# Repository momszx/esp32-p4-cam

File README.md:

# ESP32-P4-CAM

A compact WiFi streaming camera built around the ESP32-P4. The camera streams live video over WiFi (RTSP, hardware H.264). The design uses a two-board stack, FRONT and MAIN, both 45 × 45 mm, with a 7 mm gap between them. Power comes from a single USB-C port that negotiates 9 V over USB Power Delivery.

This repository holds the hardware design (KiCad 10) and its documentation. There is no firmware in it yet.

| MAIN rev A, top (F) side | MAIN rev A, bottom (B) side |
|---|---|
|  |  |

## What it is

```
USB-C (PD 9 V, 5 V fallback) ─ TVS ─ eFuse ─ buck 3.3 V ─┬─ Waveshare ESP32-P4-Module (P4 + on-module ESP32-C6)
                                                          └─ CAM_3V3 load switch ─ OV5640 camera module

OV5640 ─ MIPI CSI-2 (2 lanes) ─ ESP32-P4 ISP ─ H.264 ─ RTSP ─ esp-hosted (SDIO) ─ ESP32-C6 WiFi ─ u.FL antenna
```

- **Compute:** a [Waveshare ESP32-P4-Module](https://www.waveshare.com/wiki/ESP32-P4-Module). The module carries an ESP32-P4 with 32 MB PSRAM in the package, 16 MB of flash, and an **ESP32-C6 on the module itself**, which provides WiFi to the P4 over SDIO through esp-hosted. The module is mounted on the bottom side of MAIN and soldered by hand.
- **Camera:** an OV5640 connected over MIPI CSI-2 (2 lanes), using a 15-pin, 1.0 mm FPC with the Raspberry Pi pinout. The camera module must have its own oscillator and LDOs.
- **Power:** USB-C PD sink, VBUS limited to 9 V.
  - A WCH CH224A negotiates 9 V. It is configured with a fixed resistor strap and its PG pin goes to a GPIO.
  - A TI TPS259470 eFuse provides OVLO, UVLO, current limit, reverse blocking and auto-retry.
  - A TI TPS62933F forced-PWM buck produces the 3.3 V rail.
  - USB-C is the only power input.
- **Programming:** the first flash goes over USB-C to the P4's built-in USB-Serial-JTAG (GPIO 24/25, Full Speed only). After that, both the P4 and the C6 are updated over the air (OTA).
- **Stack:**
  - **FRONT** board: lens cut-out, IR LEDs and driver, PDM microphone.
  - **MAIN** board: everything else.
  - The two boards are joined by 4 M2 standoffs plus a 2 × 10, 1.27 mm board-to-board header (J5). The camera FFC plugs into J2 on MAIN.

Rev A is a **proof-of-concept prototype**. Its job is to prove the core path: USB-C PD → eFuse → buck → P4 → OV5640 → H.264 → RTSP over the C6. The target is 1080p30, running 24 hours without a reset. Blocks outside that path are either routed footprints that are not fitted (DNP: microSD, the IR branch) or not on the rev A board at all (rev B: the reset supervisor and the ICR; the CC-ADC tap and the Rd fallback stay in the schematic only).

## Current status (2026-10-13)

| Item | State |
|---|---|
| **MAIN rev A layout** | **Complete and reviewed.** 4 layers, JLC04101H-3313A, 45 × 45 mm. |
| Checks (`kicad-cli`, no zone refill) | **DRC 0 errors**, **0 unconnected**, **ERC 0**, **schematic ↔ board parity 0**. There are also 39 `track_width` warnings from a custom power-net rule (two of them are deliberate 0.3 mm pad-entry necks at U7); they were reviewed and accepted. |
| Ordering | **Conditional GO.** You can order once the owner checks in [`kicad/MAIN/fab/ORDERING.md`](kicad/MAIN/fab/ORDERING.md) are done: the JLC form settings, rotations in the placement preview, the USB-C shell legs, stock reservations and accepting the U5 second source (its pinout is already checked). |
| Open owner decisions | **Q6:** which side of J2 has the contacts, plus the FFC type. **Q17:** the mated height of J5. Neither one blocks PCB fabrication. The remaining BOM confirmations are listed in [`BOM_NOTES.md`](kicad/MAIN/fab/BOM_NOTES.md) §10. |
| **FRONT board** | **Not started.** Waiting on gate **G6**, which needs a stable image from MAIN bring-up (G5b) and the camera's STEP model. |
| Firmware | Not started in this repo. Rev A firmware constraints are listed in `ORDERING.md` ("Firmware rules for rev A"). |

> Since round 10 (2026-10-13) the board has **no unconnected items**. The DNP IR eFuse branch (U7, R73) is fully routed, so it can be fitted on a rev A board later without bodge wires. The CC option parts (the R4/R5 Rd fallback and the CC-ADC taps R35/R36, C29/C30, D21/D22) are in the schematic only; they are not on the rev A board.

## Key specs

| Parameter | Value |
|---|---|
| Function | WiFi live-view camera: RTSP stream, hardware H.264. Rev A target is 1080p30 (the real figure gets fixed at G0). |
| Host module | Waveshare ESP32-P4-Module: ESP32-P4NRW32 + 16 MB flash + on-module ESP32-C6H8 (SDIO). 25 × 25 × 3.3 mm, 88 castellated pads at a 1.0 mm pitch |
| Wireless | ESP32-C6 through esp-hosted. Antenna on the J4 u.FL (Hirose U.FL-R-SMT-1); the module's own IPEX connector is an alternative (antenna decision Q25 still open). |
| Camera | OV5640, MIPI CSI-2 with 2 lanes, through J2 (TE 1-84953-5, 15-pin, 1.0 mm FPC, Raspberry Pi pinout). Supplied from a switched CAM_3V3 rail (TPS22917). |
| Power input | USB-C 16-pin (HRO TYPE-C-31-M-12), USB PD sink at **9 V** via the WCH CH224A. Falls back to 5 V on a non-PD or PC port (reduced "LOW" mode). |
| Input protection | SMAJ10A TVS, plus a TI TPS259470ARPWR eFuse: UVLO 4.40 / 4.00 V, OVLO 10.87 / 9.88 V, ILIM 2.03 A, reverse blocking, auto-retry |
| 3.3 V rail | TI TPS62933F synchronous buck (FCCM): 3.33 V, 3 A, 1.2 MHz, 2.2 µH |
| Power budget (estimate, not yet measured) | About 2.2 W typical and 4.4 W peak with IR off; about 5.6 W peak at night with IR on (the IR is on FRONT). |
| MAIN PCB | 45 × 45 mm. 4 layers on **JLC04101H-3313A**, finished thickness 0.97 mm (order as 1.0 mm). ENIG finish, impedance control, components on both sides. |
| Impedance (L1 / L4, referenced to GND) | RF 50 Ω: 0.302 mm · CSI 100 Ω diff: 0.204 / 0.203 mm · USB 90 Ω diff: 0.262 / 0.203 mm |
| Layer usage | L1 signals + parts · L2 solid GND · L3 power islands + GND fill · L4 module + signals |
| Stack | FRONT + MAIN, **7 mm gap**. 4 × M2 standoffs on a 33.5 mm grid; the grid centre is (22.5; 25.0), 2.5 mm below the board centre. J5 is a 2 × 10, 1.27 mm board-to-board connector. |
| Assembly | 72 placements (47 top / 25 bottom), 40 BOM lines, all with LCSC numbers. The P4 module (U1) is soldered by hand after SMT. |
| User I/O | BOOT, RESET and USER buttons, a status LED, and 12 bottom-side test pads. The C6 UART/boot pad row (J7) is DNP. |

## Repository layout

```
.
├── README.md
├── docs/                      English documentation (primary from 2026-10-12 on)
│   ├── README.md              documentation index and conventions
│   ├── 00-requirements.md … 09-pcb-layers.md, 90-review-log.md
│   ├── img/                   board renders and routing snapshots
│   └── hu/                    Hungarian originals, frozen 2026-10-12 (no longer maintained)
├── kicad/
│   ├── MAIN/                  KiCad 10 project of the MAIN board, rev A
│   │   ├── ESP32-P4-CAM-MAIN.kicad_pro / .kicad_sch / .kicad_pcb / .kicad_dru
│   │   ├── 01_tap.kicad_sch        power: USB-C, CH224A, eFuse, buck, USB ESD
│   │   ├── 02_p4_modul.kicad_sch   ESP32-P4 module, RF/u.FL, straps, status LED, NTC
│   │   ├── 03_kamera.kicad_sch     camera FPC J2, CAM_3V3 load switch
│   │   ├── 04_prog_tp.kicad_sch    buttons, C6/UART0 pad row J7, test points
│   │   ├── 05_b2b_front.kicad_sch  J5 board-to-board header to FRONT, IR branch (DNP)
│   │   ├── 06_sd.kicad_sch         microSD (DNP)
│   │   ├── scripts/           layout automation (placement, routing, merge): see scripts/README.md
│   │   └── fab/               JLC fabrication + assembly package (Gerber, BOM, CPL, ORDERING.md); hu/ = frozen Hungarian originals
│   ├── lib/                   project library ESP32-P4-CAM: custom symbols + footprints
│   └── archive/               abandoned 2-layer 60 × 50 mm MAIN attempt (2026-10-09, not fully routed)
└── ref/                       third-party datasheets + Waveshare land pattern (local only, git-ignored)
```

`ref/` is excluded from the repository for copyright reasons. Download the files from the links in [Third-party references](#third-party-references).

## Documentation

The English documents are the primary source; [`docs/README.md`](docs/README.md) is the index, with the conventions and markers used throughout. The Hungarian originals in [`docs/hu/`](docs/hu/) (and [`kicad/MAIN/fab/hu/`](kicad/MAIN/fab/hu/)) were frozen on 2026-10-12 and are no longer maintained. **Where documents disagree, `05-architecture.md` wins.**

| Doc | Content |
|---|---|
| [00-requirements](docs/00-requirements.md) | Goal, mandatory requirements (K1–K8), extra features, document map |
| [01-esp32-p4](docs/01-esp32-p4.md) | ESP32-P4 research: variants, power, boot, camera interfaces |
| [02-esp32-c6-and-programming](docs/02-esp32-c6-and-programming.md) | C6 options, esp-hosted P4 ↔ C6 link, programming both chips, power |
| [03-camera-ov5640](docs/03-camera-ov5640.md) | OV5640 interface, FPC connector, camera power rails |
| [04-peripherals](docs/04-peripherals.md) | microSD, microphone, IR, buttons/LED, USB-C power |
| [**05-architecture**](docs/05-architecture.md) | **Authoritative.** Rev A plan (§0: fit/DNP, gates, procurement), primary-source facts, PCB stack and the frozen mechanical interface (§3.1a), stackup (§3.2), power tree and budget (§4), GPIO map, connectors, bring-up sequence (§15) |
| [06-floorplan](docs/06-floorplan.md) | Area and height budget (7 mm gap), floorplan, as-built placement |
| [07-bom-plan](docs/07-bom-plan.md) | BOM with MPN/LCSC numbers, value calculations, USB-C pin map |
| [08-diagrams](docs/08-diagrams.md) | Block and connection diagrams (Mermaid) derived from 05 |
| [09-pcb-layers](docs/09-pcb-layers.md) | As-built MAIN rev A layer plots (L1–L4, mask/silkscreen, 3D views), stackup and copper statistics |
| [90-review-log](docs/90-review-log.md) | Full history of the design and review rounds, with corrections |

## Opening and checking the design

You need **KiCad 10.0** or newer. The files use the KiCad 10 format (board version `20260206`) and do not open in KiCad 9.

1. Open `kicad/MAIN/ESP32-P4-CAM-MAIN.kicad_pro`.
   - The project library is resolved as `${KIPRJMOD}/../lib`, so keep the `kicad/` folder structure as it is.
2. Run the checks from the command line. On macOS, `kicad-cli` is at `/Applications/KiCad/KiCad.app/Contents/MacOS/kicad-cli`; on Linux and Windows it is on `PATH`.

   ```sh
   cd kicad/MAIN
   kicad-cli pcb drc --schematic-parity --severity-all --format json -o drc.json ESP32-P4-CAM-MAIN.kicad_pcb
   kicad-cli sch erc --severity-all --format json -o erc.json ESP32-P4-CAM-MAIN.kicad_sch
   ```

   Expected results:
   - DRC: **0 errors**, 39 `track_width` warnings, **0 unconnected**, **0 parity issues**.
   - ERC: **0**.
   - Write the reports somewhere outside the repo, or delete them afterwards.

3. **Refill and save zones only inside `kicad/MAIN`.**
   - The command is `kicad-cli pcb drc --refill-zones --save-board …`.
   - The `.kicad_pro` and `.kicad_dru` files must sit next to the board when you do this. If you refill outside the project folder, the project rules are lost, including the 1 mm edge clearance for power zones, and the fills come out wrong.

> [!WARNING]
> **The KiCad GUI can overwrite `.kicad_pro` with stale settings when it closes.**
>
> This has happened twice. Closing the GUI wrote back an old in-memory copy of the project, which reverted the 4-layer rules to 2-layer values. DRC then reported hundreds of errors.
>
> After every GUI session, run `git diff kicad/MAIN/ESP32-P4-CAM-MAIN.kicad_pro` and check the design rules:
> - min track 0.09 mm, min drill 0.2 mm, min via 0.45 mm, clearance 0.15 mm
> - netclasses: Default 0.15, PWR 0.4, PWR_LIGHT 0.3, RF_50 0.302, CSI_DIFF 0.204/0.203, USB 0.262/0.203
> - the `netclass_patterns`
>
> If they reverted, restore the file from git or re-run `kicad/MAIN/scripts/project_rules.py` (see the [scripts README](kicad/MAIN/scripts/README.md); it has hardcoded paths). Then re-run DRC. If scripts are modifying the board, do not keep it open in the GUI.

## Fabrication and ordering (quick start)

Everything you need is in [`kicad/MAIN/fab/`](kicad/MAIN/fab/). Start with **[`ORDERING.md`](kicad/MAIN/fab/ORDERING.md)**; the part-selection rationale is in [`BOM_NOTES.md`](kicad/MAIN/fab/BOM_NOTES.md).

1. Re-run the pre-order gate from `ORDERING.md` on the board you are about to order:
   - refill and save inside the project folder;
   - DRC without refill gives 0 errors, 0 unconnected, parity 0;
   - ERC gives 0.
   - If the board has changed, regenerate the package (`kicad-cli pcb export gerbers --check-zones …` and `pcb export drill --excellon-separate-th …`, then BOM/CPL).
2. Upload `gerber_jlc.zip`, `BOM_jlc.csv` and `CPL_jlc.csv` (72 rows) to JLCPCB.
3. Set the PCB form:
   - 4 layers, 45 × 45 mm, 1.0 mm thick;
   - **stackup JLC04101H-3313A**, **impedance control on**, **ENIG**;
   - tented vias;
   - frame rails on the top and bottom edges only, with **no tab on the right edge**.
4. Check rotation and pin 1 in the JLC placement preview, and decide how the USB-C shell legs get soldered.
5. Reserve the low-stock parts before you order.
6. The P4 module is **not** in the BOM. Solder it by hand, then do the pre-power ohmmeter checks from `ORDERING.md`.

## Design-review history

- **Round 7 (2026-10-10):** a 15-agent PCB review (7 domain experts, a sceptical re-measurer for each domain, and a gap-finder who wrote the summary) gave **NO-GO**. Findings included the buck hot loop, the RF reference plane, GND stitching, the BOM gate and the ESP_EN pull-up.
- **Round 8 (2026-10-10/11):** **two parallel fix passes**. Each agent worked on its own fenced board region and the changes were merged by UUID (`kicad/MAIN/scripts/pcbmerge.py`, `regioncheck.py`). An independent checker re-measured every fix.
- **Round 9 (2026-10-11):** a 16-agent final review gave **conditional GO**. No design changes were needed. The only critical item was stale zone fills, a process issue, fixed by refilling and saving inside the project folder.
- **Round 10 (2026-10-13):** an external reviewer flagged the 12 unconnected items on DNP parts that rounds 8/9 had accepted. The IR eFuse branch (U7/R73) was routed so it can be fitted later. A routing attempt for the CC option group failed the independent check, so those 8 parts stay in the schematic only and are no longer on the board. Result: **0 unconnected**, BOM and CPL unchanged.

Details are in [`docs/90-review-log.md`](docs/90-review-log.md).

## Gates (rev A)

Full definitions and exit criteria are in [`05-architecture.md` §0.2](docs/05-architecture.md).

| Gate | Content | Status |
|---|---|---|
| G0 | Dev-kit stream test: OV5640 → ISP → H.264 → RTSP over the C6, a 24-hour soak, and current measurements. Freeze the SDK and component versions. | open |
| G1 | CH224A breakout bench test: 9 V PDO, strap, PG polarity, DP/DM left unconnected | open |
| G2 | Module schematic, footprint and antenna decision | partial: footprint built from the Waveshare land pattern and verified; module schematic questions and antenna choice still open |
| G3 | Freeze the camera module: lens, STEP model, FFC lengths, final J2 contact side (Q6) and CSI pin order (Q24) | open |
| G4 | BOM sheet complete (MPN / LCSC for every fitted part) | **closed for rev A** (2026-10-11) |
| G5 | MAIN schematic → layout → DRC → order | layout done, **conditional GO**; next is the order (see ORDERING.md) |
| G5b | Bring-up: MAIN on its own, camera on a 50–100 mm FFC, CSI soak test with error counters | pending |
| G6 | FRONT board: IR, microphone (ICR in rev B) | not started; begins after G5b |

## Third-party references

The datasheets are **not** redistributed in this repository. Get them from the vendors:

- **TI TPS25947 / TPS259470 eFuse** (the TPS259470ARPWR is a TPS25947xx variant). Datasheet SLVSFC9: <https://www.ti.com/lit/ds/symlink/tps25947.pdf>. Product page: <https://www.ti.com/product/TPS25947>
- **TI TPS62933 / TPS62933F buck.** Datasheet SLUSEA4: <https://www.ti.com/lit/ds/symlink/tps62933.pdf>. Product page: <https://www.ti.com/product/TPS62933>
- **WCH CH224 (CH224A / CH224Q) USB PD sink.** Product page: <https://www.wch-ic.com/products/CH224.html> (Chinese site: <https://www.wch.cn/products/CH224.html>). The design used the Chinese datasheet "CH224 手册1", v2.1.
- **Waveshare ESP32-P4-Module.** Wiki with pinout, schematic and the PCB land-pattern ZIP: <https://www.waveshare.com/wiki/ESP32-P4-Module>
- **Espressif ESP32-P4:**
  - product page: <https://www.espressif.com/en/products/socs/esp32-p4>
  - datasheet: <https://www.espressif.com/sites/default/files/documentation/esp32-p4_datasheet_en.pdf>
  - technical reference manual: <https://www.espressif.com/sites/default/files/documentation/esp32-p4_technical_reference_manual_en.pdf>
  - ESP-IDF programming guide: <https://docs.espressif.com/projects/esp-idf/en/latest/esp32p4/>
- **Related software:**
  - esp-hosted-mcu: <https://github.com/espressif/esp-hosted-mcu>
  - esp-video-components (esp_cam_sensor): <https://github.com/espressif/esp-video-components>
- **Stackup and impedance:** JLCPCB impedance calculator: <https://jlcpcb.com/pcb-impedance-calculator>

## License

Private project — all rights reserved (no license granted yet).

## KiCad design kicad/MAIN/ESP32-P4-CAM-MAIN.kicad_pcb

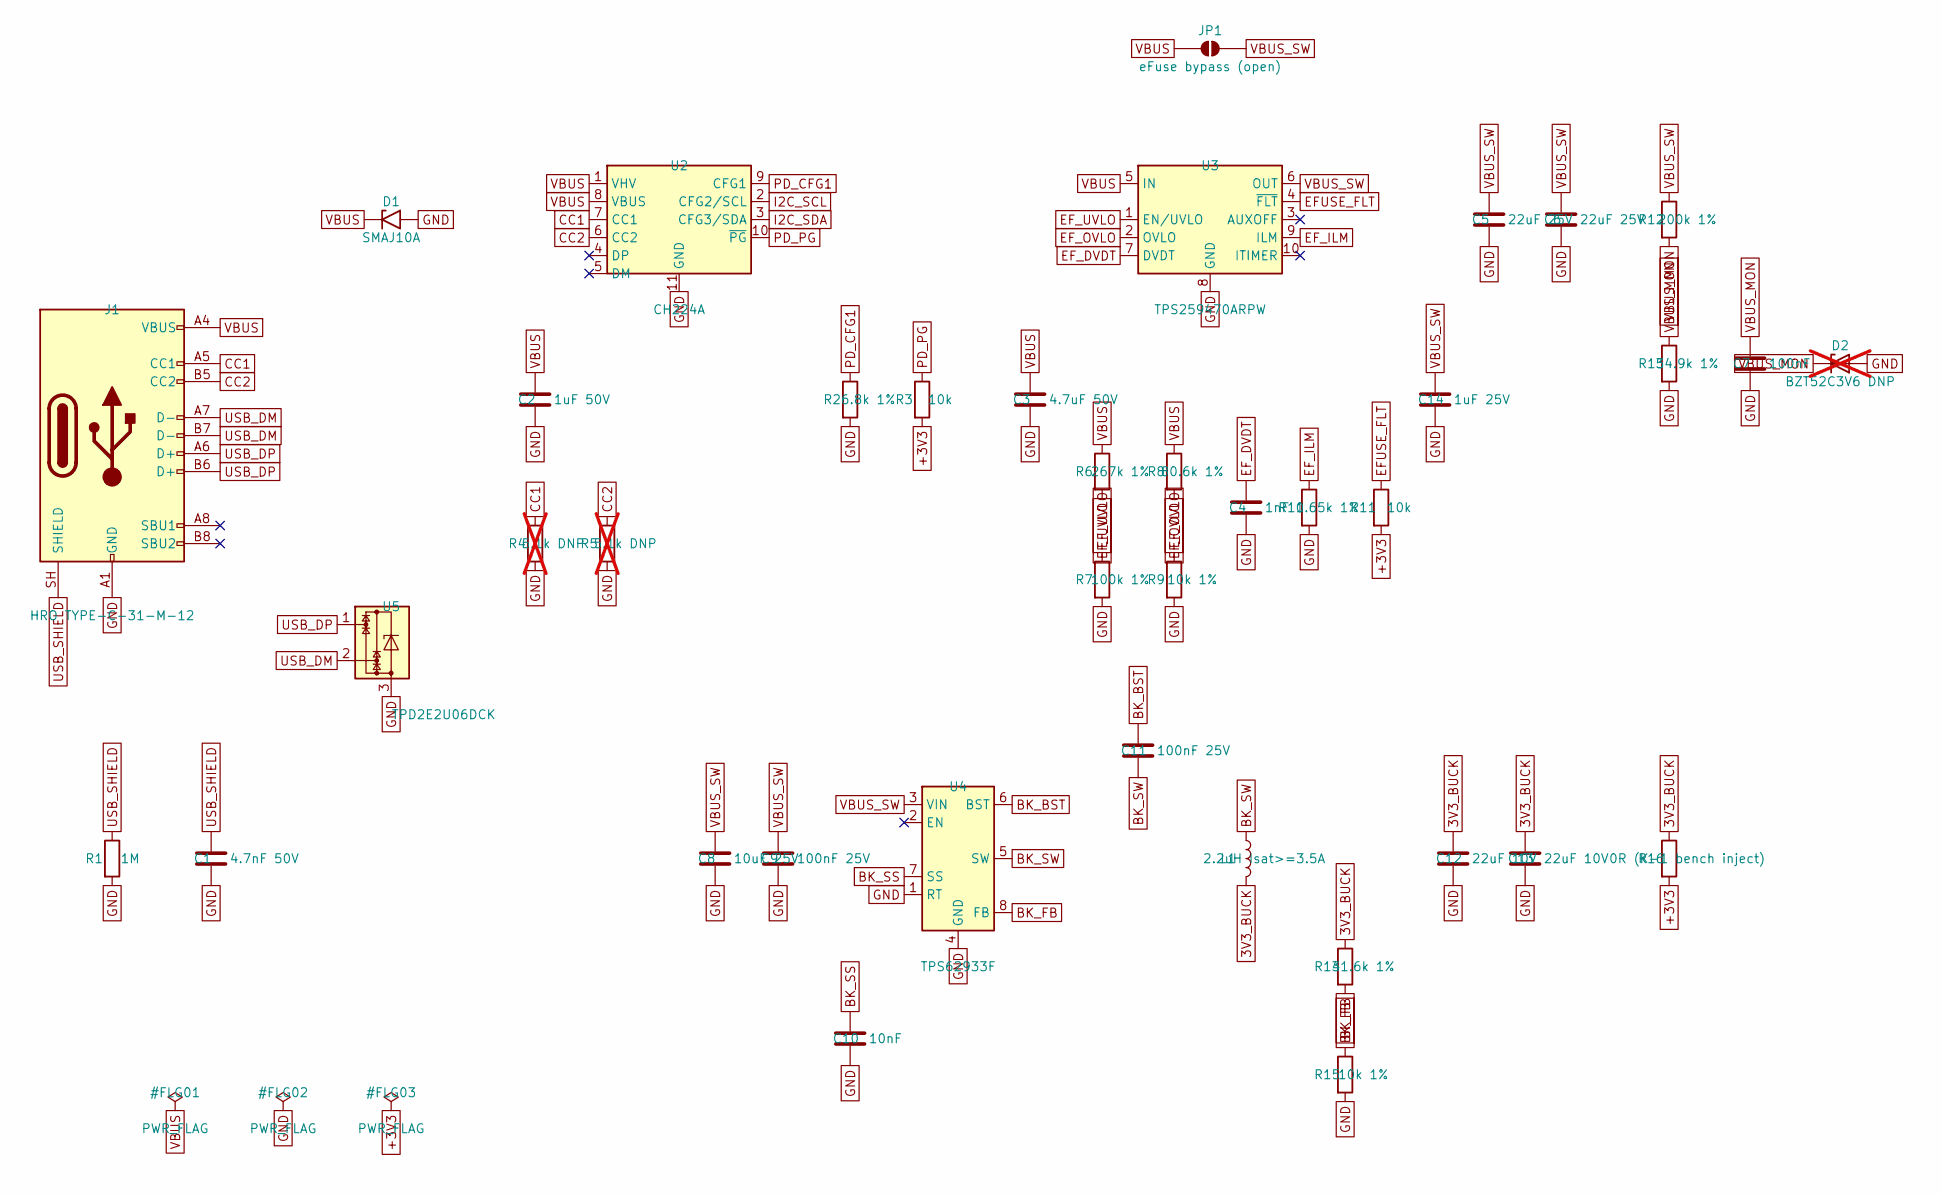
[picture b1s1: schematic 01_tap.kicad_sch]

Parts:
C1: 4.7nF 50V; C_0603_1608Metric; MPN CC0603KRX7RABB472; LCSC C596328
C2: 1uF 50V; C_0603_1608Metric; MPN CL10A105KB8NNNC; LCSC C15849
C3: 4.7uF 50V; C_0805_2012Metric; MPN CL21A475KBQNNNE; LCSC C98192
C4: 1nF; C_0603_1608Metric; MPN CL10B102KB8NNNC; LCSC C1588
C5, C6: 22uF 25V; C_1210_3225Metric; MPN CL32A226KAJNNNE; LCSC C52306
C7: 100nF; C_0603_1608Metric; MPN CC0603KRX7R9BB104; LCSC C14663
C8: 10uF 25V; C_0805_2012Metric; MPN CL21A106KAYNNNE; LCSC C15850
C9, C11: 100nF 25V; C_0603_1608Metric; MPN CC0603KRX7R9BB104; LCSC C14663
C10: 10nF; C_0603_1608Metric; MPN 0603B103K500NT; LCSC C57112
C12, C13: 22uF 10V; C_0805_2012Metric; MPN CL21A226MAQNNNE; LCSC C45783
C14: 1uF 25V; C_0603_1608Metric; MPN CL10B105KA8NNNC; LCSC C29936
D1: SMAJ10A; D_SMA; MPN SMAJ10A-13-F; LCSC C134939
D2: BZT52C3V6 DNP; D_SOD-123; not fitted
J1: HRO TYPE-C-31-M-12; USB_C_Receptacle_HRO_TYPE-C-31-M-12; MPN TYPE-C-31-M-12; LCSC C165948
JP1: eFuse bypass (open); SolderJumper-2_P1.3mm_Open_RoundedPad1.0x1.5mm
L1: 2.2uH Isat>=3.5A; L_Taiyo-Yuden_NR-50xx; MPN NRS5024T2R2NMGJ; LCSC C222926
R1: 1M; R_0603_1608Metric; MPN 0603WAF1004T5E; LCSC C22935
R2: 6.8k 1%; R_0603_1608Metric; MPN 0603WAF6801T5E; LCSC C23212
R3, R11: 10k; R_0603_1608Metric; MPN 0603WAF1002T5E; LCSC C25804
R4, R5: 5.1k DNP; R_0603_1608Metric; not fitted
R6: 267k 1%; R_0603_1608Metric; MPN 0603WAF2673T5E; LCSC C22963
R7: 100k 1%; R_0603_1608Metric; MPN 0603WAF1003T5E; LCSC C25803
R8: 80.6k 1%; R_0603_1608Metric; MPN 0603WAF8062T5E; LCSC C23249
R9, R15: 10k 1%; R_0603_1608Metric; MPN 0603WAF1002T5E; LCSC C25804
R10: 1.65k 1%; R_0603_1608Metric; MPN 0603WAF1651T5E; LCSC C22845
R12: 200k 1%; R_0603_1608Metric; MPN 0603WAF2003T5E; LCSC C25811
R13: 54.9k 1%; R_0603_1608Metric; MPN 0603WAF5492T5E; LCSC C23077
R14: 31.6k 1%; R_0603_1608Metric; MPN 0603WAF3162T5E; LCSC C25967
R16: 0R (K-1 bench inject); R_0805_2012Metric; MPN 0805W8F0000T5E; LCSC C17477
U2: CH224A; SSOP-10-1EP_3.9x4.9mm_P1mm_EP2.1x3.3mm; MPN CH224A; LCSC C42459160
U3: TPS259470ARPW; TI_RPW0010A_VQFN-HR-10_2x2mm; MPN TPS259470ARPWR; LCSC C3662799
U4: TPS62933F; SOT-583-8; MPN TPS62933FDRLR; LCSC C5219272
U5: TPD2E2U06DCK; SOT-323_SC-70; MPN TPD2E2U06DCKR-TP; LCSC C5350871

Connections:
3V3_BUCK: C12.1, C13.1, L1.2, R14.1, R16.1
+3V3: R3.2, R11.2, R16.2; also elsewhere on the board
BK_BST: C11.1, U4.6 (BST)
BK_FB: R14.2, R15.1, U4.8 (FB)
BK_SS: C10.1, U4.7 (SS)
BK_SW: C11.2, L1.1, U4.5 (SW)
CC1: J1.A5 (CC1), R4.1, U2.7 (CC1)
CC2: J1.B5 (CC2), R5.1, U2.6 (CC2)
EFUSE_FLT: R11.1, U3.4 (~FLT); also elsewhere on the board
EF_DVDT: C4.1, U3.7 (DVDT)
EF_ILM: R10.1, U3.9 (ILM)
EF_OVLO: R8.2, R9.1, U3.2 (OVLO)
EF_UVLO: R6.2, R7.1, U3.1 (EN/UVLO)
GND: C1.2, C2.2, C3.2, C4.2, C5.2, C6.2, C7.2, C8.2, C9.2, C10.2, C12.2, C13.2, C14.2, D1.2 (A2), D2.2 (A), J1.A1 (GND), J1.A12 (GND), J1.B1 (GND), J1.B12 (GND), R1.2, R2.2, R4.2, R5.2, R7.2, R9.2, R10.2, R13.2, R15.2, U2.11 (GND), U3.8 (GND), U4.1 (RT), U4.4 (GND), U5.3; also elsewhere on the board
I2C_SCL: U2.2 (CFG2/SCL); also elsewhere on the board
I2C_SDA: U2.3 (CFG3/SDA); also elsewhere on the board
PD_CFG1: R2.1, U2.9 (CFG1)
PD_PG: R3.1, U2.10 (~PG); also elsewhere on the board
USB_DM: J1.A7 (D-), J1.B7 (D-), U5.2; also elsewhere on the board
USB_DP: J1.A6 (D+), J1.B6 (D+), U5.1; also elsewhere on the board
USB_SHIELD: C1.1, J1.SH (SHIELD), R1.1
VBUS: C2.1, C3.1, D1.1 (A1), J1.A4 (VBUS), J1.A9 (VBUS), J1.B4 (VBUS), J1.B9 (VBUS), JP1.1 (A), R6.1, R8.1, U2.1 (VHV), U2.8 (VBUS), U3.5 (IN); also elsewhere on the board
VBUS_MON: C7.1, D2.1 (K), R12.2, R13.1; also elsewhere on the board
VBUS_SW: C5.1, C6.1, C8.1, C9.1, C14.1, JP1.2 (B), R12.1, U3.6 (OUT), U4.3 (VIN); also elsewhere on the board

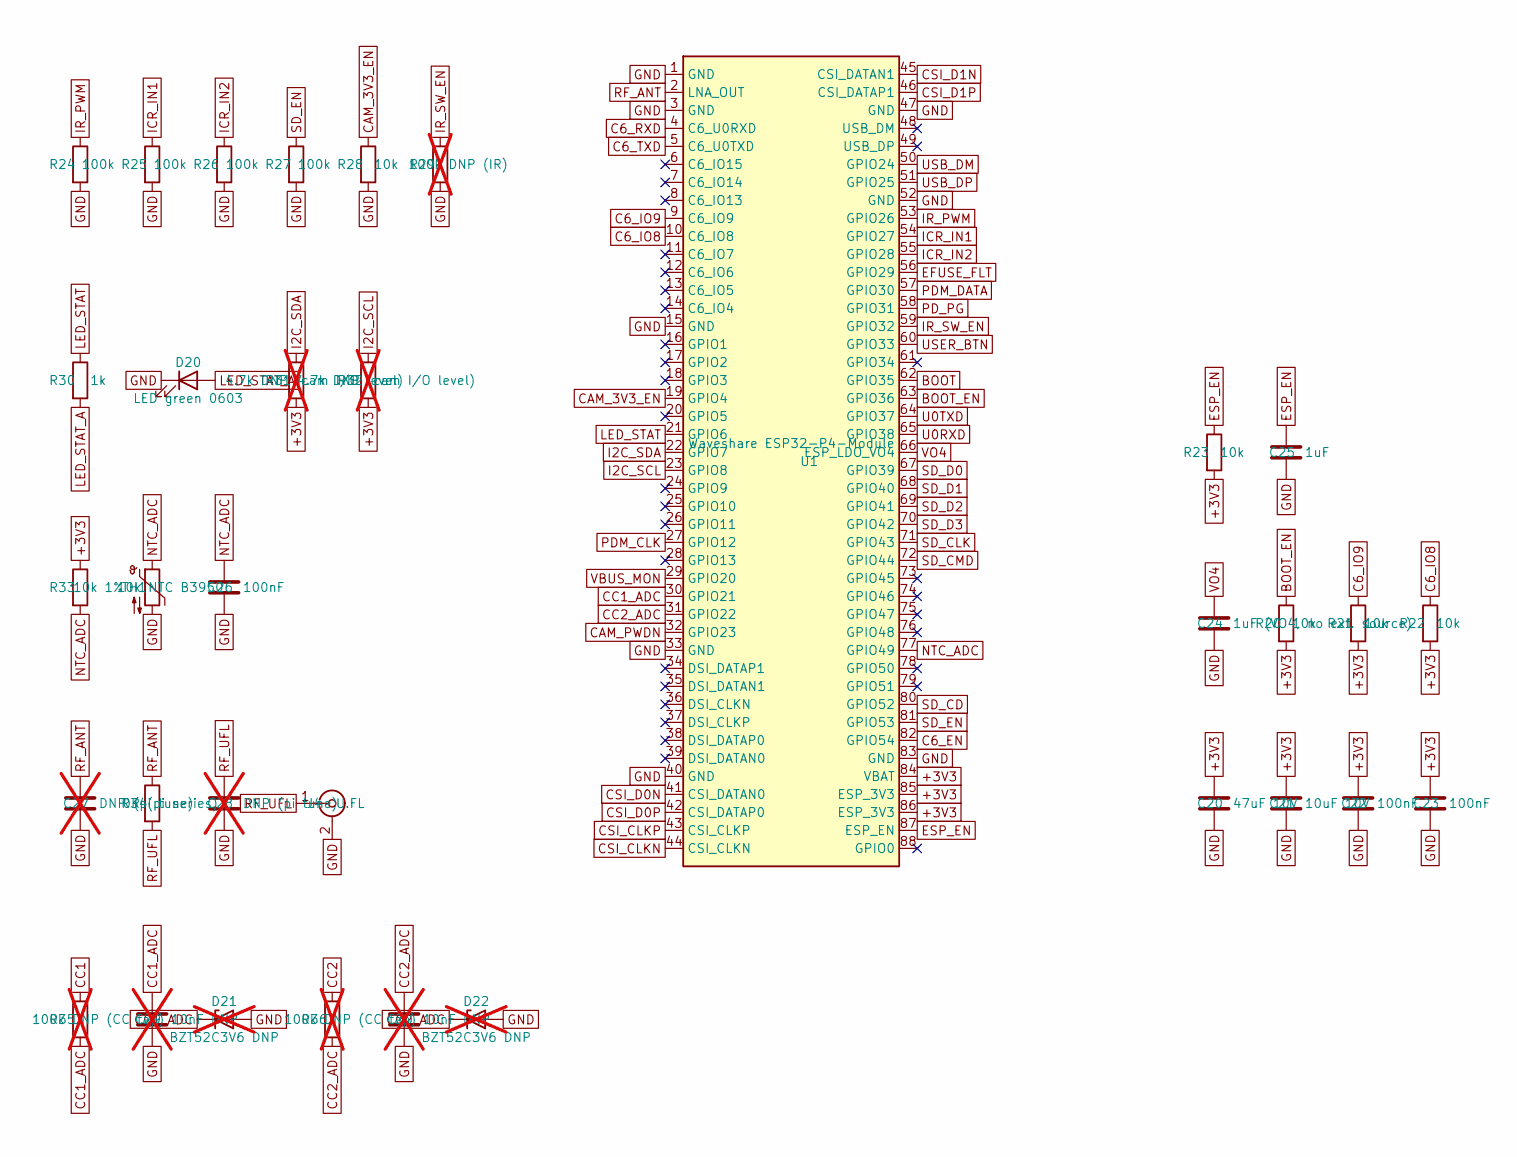
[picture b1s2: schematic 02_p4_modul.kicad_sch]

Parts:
C20: 47uF 10V; C_1210_3225Metric; MPN GRM32ER61C476KE15L; LCSC C77101
C21: 10uF 10V; C_0805_2012Metric; MPN CL21A106KAYNNNE; LCSC C15850
C22, C23, C26: 100nF; C_0603_1608Metric; MPN CC0603KRX7R9BB104; LCSC C14663
C24: 1uF (VO4, no ext. source); C_0603_1608Metric; MPN CL10A105KB8NNNC; LCSC C15849
C25: 1uF; C_0603_1608Metric; MPN CL10A105KB8NNNC; LCSC C15849
C27, C28: DNP (pi tune); C_0402_1005Metric; not fitted
C29, C30: 10nF DNP; C_0603_1608Metric; not fitted
D20: LED green 0603; LED_0603_1608Metric; MPN KT-0603G; LCSC C12624
D21, D22: BZT52C3V6 DNP; D_SOD-123; not fitted
J4: U.FL; U.FL_Hirose_U.FL-R-SMT-1_Vertical; MPN U.FL-R-SMT-1(80); LCSC C88374
R20, R21, R22, R23, R28: 10k; R_0603_1608Metric; MPN 0603WAF1002T5E; LCSC C25804
R24, R25, R26, R27: 100k; R_0603_1608Metric; MPN 0603WAF1003T5E; LCSC C25803
R29: 100k DNP (IR); R_0603_1608Metric; not fitted
R30: 1k; R_0603_1608Metric; MPN 0603WAF1001T5E; LCSC C21190
R31, R32: 4.7k DNP (cam I/O level); R_0603_1608Metric; not fitted
R33: 10k 1%; R_0603_1608Metric; MPN 0603WAF1002T5E; LCSC C25804
R34: 0R (pi series); R_0402_1005Metric; MPN 0402WGF0000TCE; LCSC C17168
R35, R36: 100k DNP (CC tap); R_0603_1608Metric; not fitted
TH1: 10k NTC B3950; R_0603_1608Metric; MPN KNTC0603/10KF3950; LCSC C2892547
U1: Waveshare ESP32-P4-Module; Waveshare_ESP32-P4-Module_HandSolder

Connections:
+3V3: C20.1, C21.1, C22.1, C23.1, R20.2, R21.2, R22.2, R23.2, R31.2, R32.2, R33.1, U1.84 (VBAT), U1.85 (ESP_3V3), U1.86 (ESP_3V3); also elsewhere on the board
BOOT: U1.62 (GPIO35); also elsewhere on the board
BOOT_EN: R20.1, U1.63 (GPIO36)
C6_EN: U1.82 (GPIO54); also elsewhere on the board
C6_IO8: R22.1, U1.10 (C6_IO8); also elsewhere on the board
C6_IO9: R21.1, U1.9 (C6_IO9); also elsewhere on the board
C6_RXD: U1.4 (C6_U0RXD); also elsewhere on the board
C6_TXD: U1.5 (C6_U0TXD); also elsewhere on the board
CAM_3V3_EN: R28.1, U1.19 (GPIO4); also elsewhere on the board
CAM_PWDN: U1.32 (GPIO23); also elsewhere on the board
CC1_ADC: C29.1, D21.1 (K), R35.2, U1.30 (GPIO21)
CC2_ADC: C30.1, D22.1 (K), R36.2, U1.31 (GPIO22)
CSI_CLKN: U1.44 (CSI_CLKN); also elsewhere on the board
CSI_CLKP: U1.43 (CSI_CLKP); also elsewhere on the board
CSI_D0N: U1.41 (CSI_DATAN0); also elsewhere on the board
CSI_D0P: U1.42 (CSI_DATAP0); also elsewhere on the board
CSI_D1N: U1.45 (CSI_DATAN1); also elsewhere on the board
CSI_D1P: U1.46 (CSI_DATAP1); also elsewhere on the board
EFUSE_FLT: U1.56 (GPIO29); also elsewhere on the board
ESP_EN: C25.1, R23.1, U1.87 (ESP_EN); also elsewhere on the board
GND: C20.2, C21.2, C22.2, C23.2, C24.2, C25.2, C26.2, C27.2, C28.2, C29.2, C30.2, D20.1 (K), D21.2 (A), D22.2 (A), J4.2 (Ext), R24.2, R25.2, R26.2, R27.2, R28.2, R29.2, TH1.2, U1.1 (GND), U1.3 (GND), U1.15 (GND), U1.33 (GND), U1.40 (GND), U1.47 (GND), U1.52 (GND), U1.83 (GND); also elsewhere on the board
I2C_SCL: R32.1, U1.23 (GPIO8); also elsewhere on the board
I2C_SDA: R31.1, U1.22 (GPIO7); also elsewhere on the board
ICR_IN1: R25.1, U1.54 (GPIO27); also elsewhere on the board
ICR_IN2: R26.1, U1.55 (GPIO28); also elsewhere on the board
IR_PWM: R24.1, U1.53 (GPIO26); also elsewhere on the board
IR_SW_EN: R29.1, U1.59 (GPIO32); also elsewhere on the board
LED_STAT: R30.1, U1.21 (GPIO6)
LED_STAT_A: D20.2 (A), R30.2
NTC_ADC: C26.1, R33.2, TH1.1, U1.77 (GPIO49)
PDM_CLK: U1.27 (GPIO12); also elsewhere on the board
PDM_DATA: U1.57 (GPIO30); also elsewhere on the board
PD_PG: U1.58 (GPIO31); also elsewhere on the board
RF_ANT: C27.1, R34.1, U1.2 (LNA_OUT)
RF_UFL: C28.1, J4.1 (In), R34.2
SD_CD: U1.80 (GPIO52); also elsewhere on the board
SD_CLK: U1.71 (GPIO43); also elsewhere on the board
SD_CMD: U1.72 (GPIO44); also elsewhere on the board
SD_D0: U1.67 (GPIO39); also elsewhere on the board
SD_D1: U1.68 (GPIO40); also elsewhere on the board
SD_D2: U1.69 (GPIO41); also elsewhere on the board
SD_D3: U1.70 (GPIO42); also elsewhere on the board
SD_EN: R27.1, U1.81 (GPIO53); also elsewhere on the board
U0RXD: U1.65 (GPIO38); also elsewhere on the board
U0TXD: U1.64 (GPIO37); also elsewhere on the board
USB_DM: U1.50 (GPIO24); also elsewhere on the board
USB_DP: U1.51 (GPIO25); also elsewhere on the board
USER_BTN: U1.60 (GPIO33); also elsewhere on the board
VBUS_MON: U1.29 (GPIO20); also elsewhere on the board
VO4: C24.1, U1.66 (ESP_LDO_VO4); also elsewhere on the board

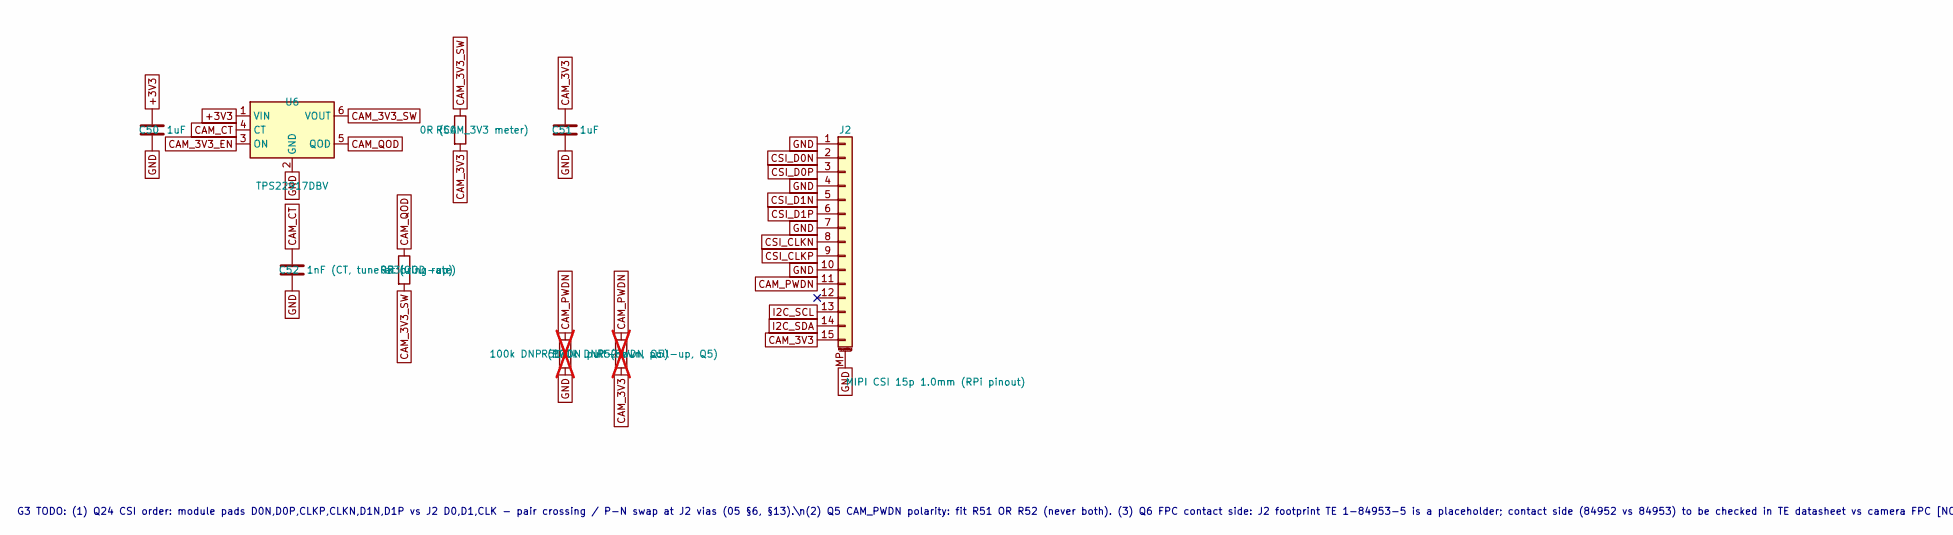
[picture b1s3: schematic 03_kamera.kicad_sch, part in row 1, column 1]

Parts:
C50, C51: 1uF; C_0603_1608Metric; MPN CL10A105KB8NNNC; LCSC C15849
C52: 1nF (CT, tune at bring-up); C_0603_1608Metric; MPN CL10B102KB8NNNC; LCSC C1588
J2: MIPI CSI 15p 1.0mm (RPi pinout); TE_1-84953-5_1x15-1MP_P1.0mm_Horizontal; MPN 1-84953-5; LCSC C5164008
R50: 0R (CAM_3V3 meter); R_0603_1608Metric; MPN 0603WAF0000T5E; LCSC C21189
R51: 100k DNP (PWDN pull-down, Q5); R_0603_1608Metric; not fitted
R52: 100k DNP (PWDN pull-up, Q5); R_0603_1608Metric; not fitted
R53: 0R (QOD rate); R_0603_1608Metric; MPN 0603WAF0000T5E; LCSC C21189
U6: TPS22917DBV; SOT-23-6; MPN TPS22917DBVR; LCSC C2681320

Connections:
+3V3: C50.1, U6.1 (VIN); also elsewhere on the board
CAM_3V3: C51.1, J2.15, R50.2, R52.2; also elsewhere on the board
CAM_3V3_EN: U6.3 (ON); also elsewhere on the board
CAM_3V3_SW: R50.1, R53.2, U6.6 (VOUT)
CAM_CT: C52.1, U6.4 (CT)
CAM_PWDN: J2.11, R51.1, R52.1; also elsewhere on the board
CAM_QOD: R53.1, U6.5 (QOD)
CSI_CLKN: J2.8; also elsewhere on the board
CSI_CLKP: J2.9; also elsewhere on the board
CSI_D0N: J2.2; also elsewhere on the board
CSI_D0P: J2.3; also elsewhere on the board
CSI_D1N: J2.5; also elsewhere on the board
CSI_D1P: J2.6; also elsewhere on the board
GND: C50.2, C51.2, C52.2, J2.1, J2.4, J2.7, J2.10, J2.MP (MountPin), R51.2, U6.2 (GND); also elsewhere on the board
I2C_SCL: J2.13; also elsewhere on the board
I2C_SDA: J2.14; also elsewhere on the board

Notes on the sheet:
G3 TODO: (1) Q24 CSI order: module pads D0N,D0P,CLKP,CLKN,D1N,D1P vs J2 D0,D1,CLK - pair crossing / P-N swap at J2 vias (05 §6, §13).\n(2) Q5 CAM_PWDN polarity: fit R51 OR R52 (never both). (3) Q6 FPC contact side: J2 footprint TE 1-84953-5 is a placeholder; contact side (84952 vs 84953) to be chec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

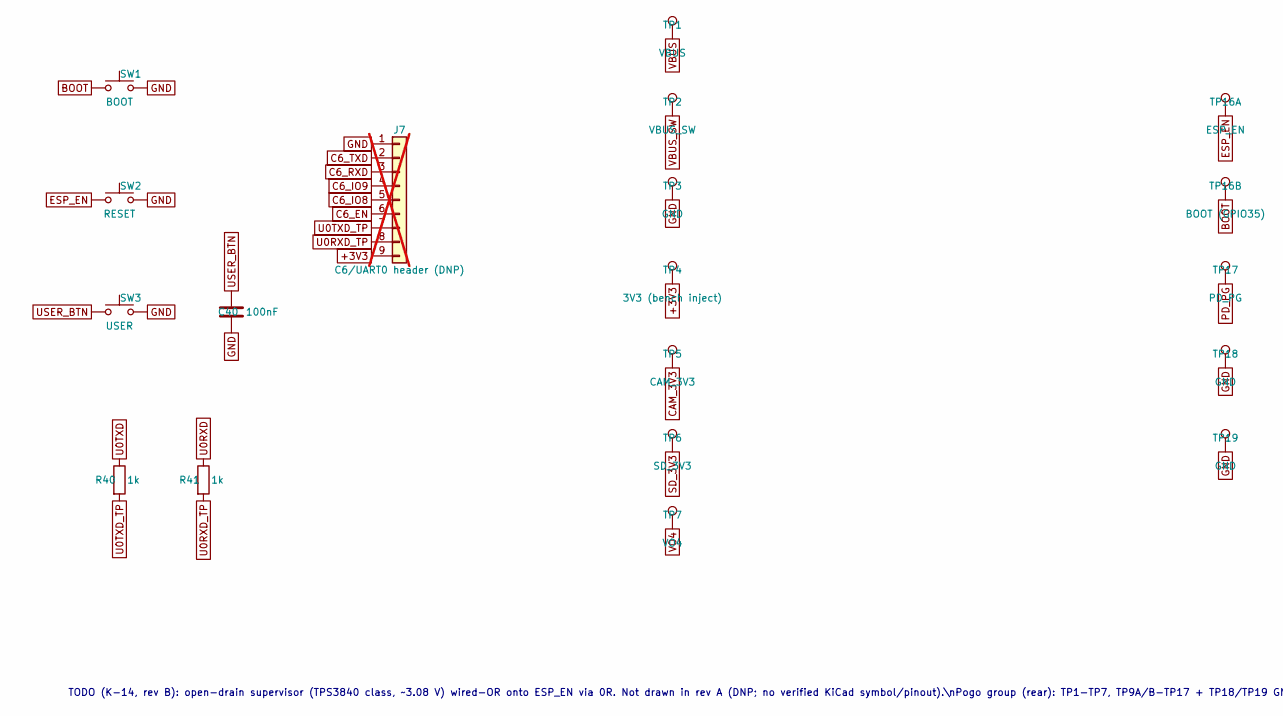
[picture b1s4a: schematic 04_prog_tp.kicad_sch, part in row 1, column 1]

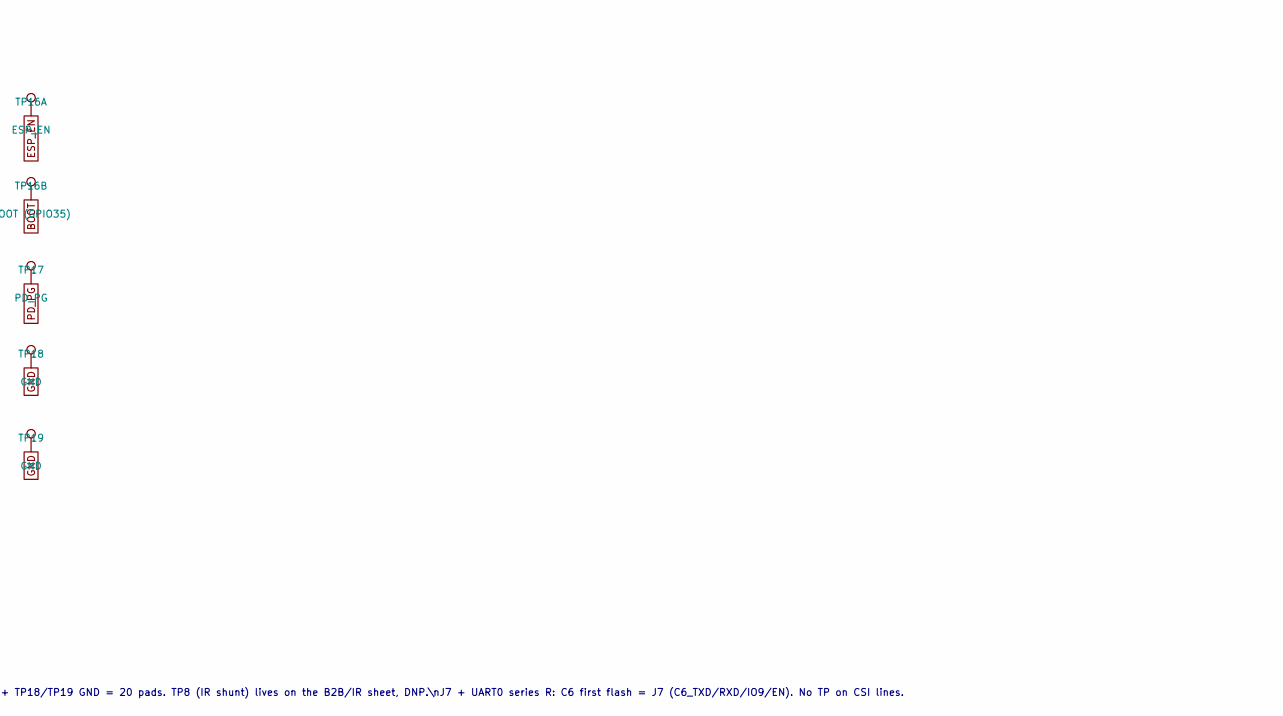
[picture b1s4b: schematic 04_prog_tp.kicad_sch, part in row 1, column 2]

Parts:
C40: 100nF; C_0603_1608Metric; MPN CC0603KRX7R9BB104; LCSC C14663
J7: C6/UART0 header (DNP); PadRow_1x09_P1.27mm_SMD; not fitted
R40, R41: 1k; R_0603_1608Metric; MPN 0603WAF1001T5E; LCSC C21190
SW1: BOOT; SW_SPST_B3U-1000P; MPN B3U-1000P; LCSC C231329
SW2: RESET; SW_SPST_B3U-1000P; MPN B3U-1000P; LCSC C231329
SW3: USER; SW_SPST_B3U-1000P; MPN B3U-1000P; LCSC C231329
TP1: VBUS; TestPoint_Pad_D1.5mm
TP2: VBUS_SW; TestPoint_Pad_D1.5mm
TP3, TP18, TP19: GND; TestPoint_Pad_D1.5mm
TP4: 3V3 (bench inject); TestPoint_Pad_D1.5mm
TP5: CAM_3V3; TestPoint_Pad_D1.5mm
TP6: SD_3V3; TestPoint_Pad_D1.5mm
TP7: VO4; TestPoint_Pad_D1.5mm
TP16A: ESP_EN; TestPoint_Pad_D1.5mm
TP16B: BOOT (GPIO35); TestPoint_Pad_D1.5mm
TP17: PD_PG; TestPoint_Pad_D1.5mm

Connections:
+3V3: J7.9, TP4.1; also elsewhere on the board
BOOT: SW1.1, TP16B.1; also elsewhere on the board
C6_EN: J7.6; also elsewhere on the board
C6_IO8: J7.5; also elsewhere on the board
C6_IO9: J7.4; also elsewhere on the board
C6_RXD: J7.3; also elsewhere on the board
C6_TXD: J7.2; also elsewhere on the board
CAM_3V3: TP5.1; also elsewhere on the board
ESP_EN: SW2.1, TP16A.1; also elsewhere on the board
GND: C40.2, J7.1, SW1.2, SW2.2, SW3.2, TP3.1, TP18.1, TP19.1; also elsewhere on the board
PD_PG: TP17.1; also elsewhere on the board
SD_3V3: TP6.1; also elsewhere on the board
U0RXD: R41.1; also elsewhere on the board
U0RXD_TP: J7.8, R41.2
U0TXD: R40.1; also elsewhere on the board
U0TXD_TP: J7.7, R40.2
USER_BTN: C40.1, SW3.1; also elsewhere on the board
VBUS: TP1.1; also elsewhere on the board
VBUS_SW: TP2.1; also elsewhere on the board
VO4: TP7.1; also elsewhere on the board

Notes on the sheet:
TODO (K-14, rev B): open-drain supervisor (TPS3840 class, ~3.08 V) wired-OR onto ESP_EN via 0R. Not drawn in rev A (DNP; no verified KiCad symbol/pinout).\nPogo group (rear): TP1-TP7, TP9A/B-TP17 + TP18/TP19 GND = 20 pads. TP8 (IR shunt) lives on the B2B/IR sheet, DNP.\nJ7 + UART0 series R: C6 firs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

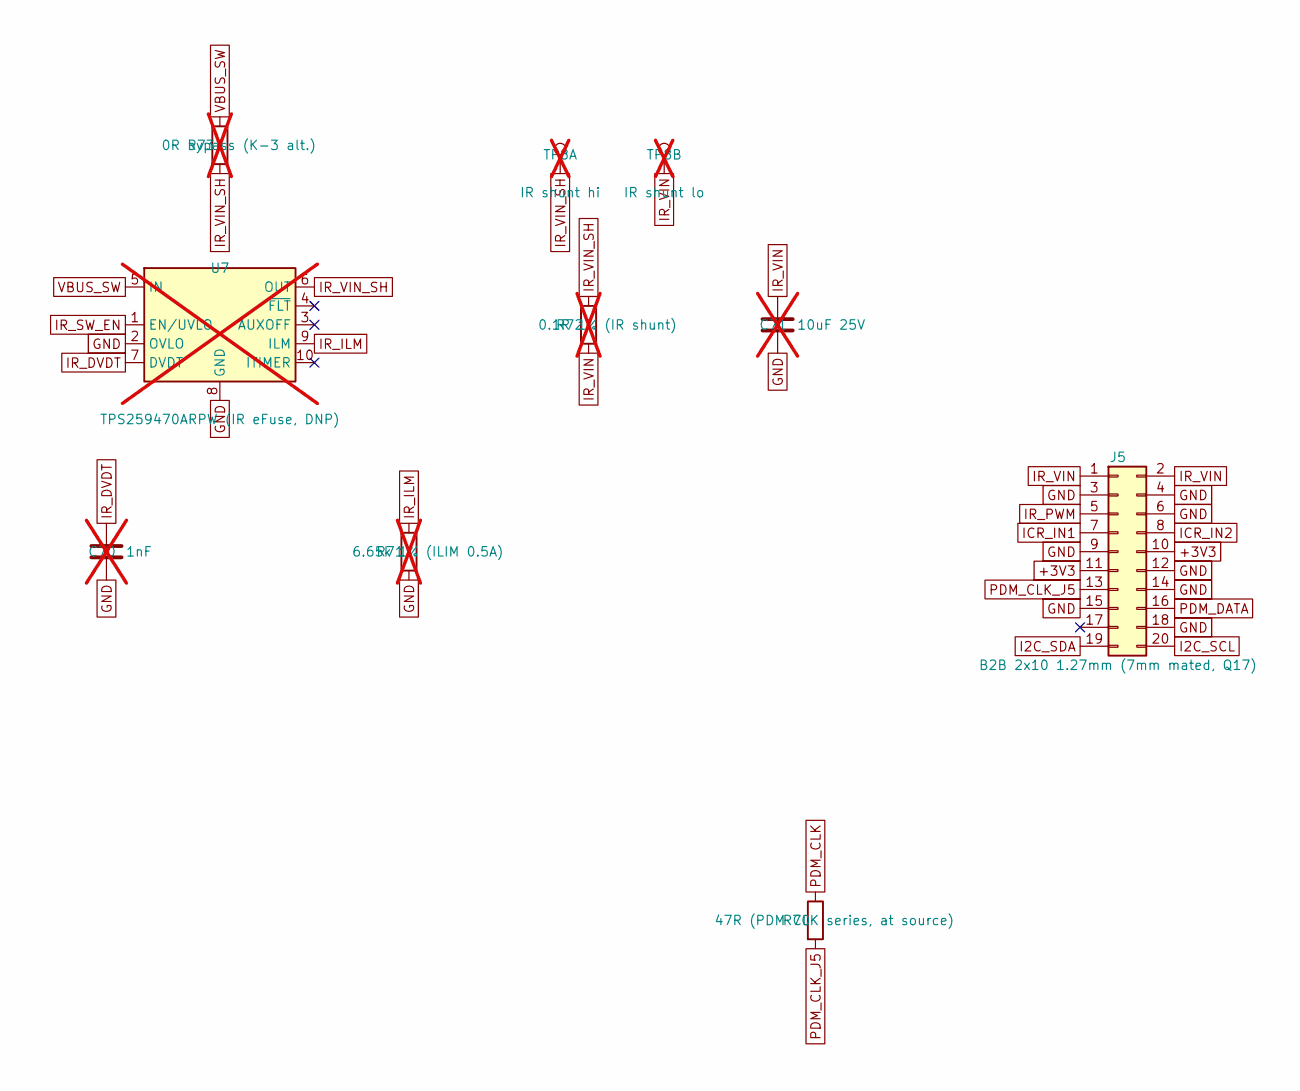
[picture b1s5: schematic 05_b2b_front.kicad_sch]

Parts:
C70: 1nF; C_0603_1608Metric; not fitted
C71: 10uF 25V; C_0805_2012Metric; not fitted
J5: B2B 2x10 1.27mm (7mm mated, Q17); PinHeader_2x10_P1.27mm_Vertical_SMD; MPN HC-PZ127-7.2L-2x10PS; LCSC C41375929
R70: 47R (PDM CLK series, at source); R_0603_1608Metric; MPN 0603WAF470JT5E; LCSC C23182
R71: 6.65k 1% (ILIM 0.5A); R_0603_1608Metric; not fitted
R72: 0.1R 1% (IR shunt); R_0805_2012Metric; not fitted
R73: 0R bypass (K-3 alt.); R_0805_2012Metric; not fitted
TP8A: IR shunt hi; TestPoint_Pad_D1.5mm; not fitted
TP8B: IR shunt lo; TestPoint_Pad_D1.5mm; not fitted
U7: TPS259470ARPW (IR eFuse, DNP); TI_RPW0010A_VQFN-HR-10_2x2mm; not fitted

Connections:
+3V3: J5.10, J5.11; also elsewhere on the board
GND: C70.2, C71.2, J5.3, J5.4, J5.6, J5.9, J5.12, J5.14, J5.15, J5.18, R71.2, U7.2 (OVLO), U7.8 (GND); also elsewhere on the board
I2C_SCL: J5.20; also elsewhere on the board
I2C_SDA: J5.19; also elsewhere on the board
ICR_IN1: J5.7; also elsewhere on the board
ICR_IN2: J5.8; also elsewhere on the board
IR_DVDT: C70.1, U7.7 (DVDT)
IR_ILM: R71.1, U7.9 (ILM)
IR_PWM: J5.5; also elsewhere on the board
IR_SW_EN: U7.1 (EN/UVLO); also elsewhere on the board
IR_VIN: C71.1, J5.1, J5.2, R72.2, TP8B.1
IR_VIN_SH: R72.1, R73.2, TP8A.1, U7.6 (OUT)
PDM_CLK: R70.1; also elsewhere on the board
PDM_CLK_J5: J5.13, R70.2
PDM_DATA: J5.16; also elsewhere on the board
VBUS_SW: R73.1, U7.5 (IN); also elsewhere on the board

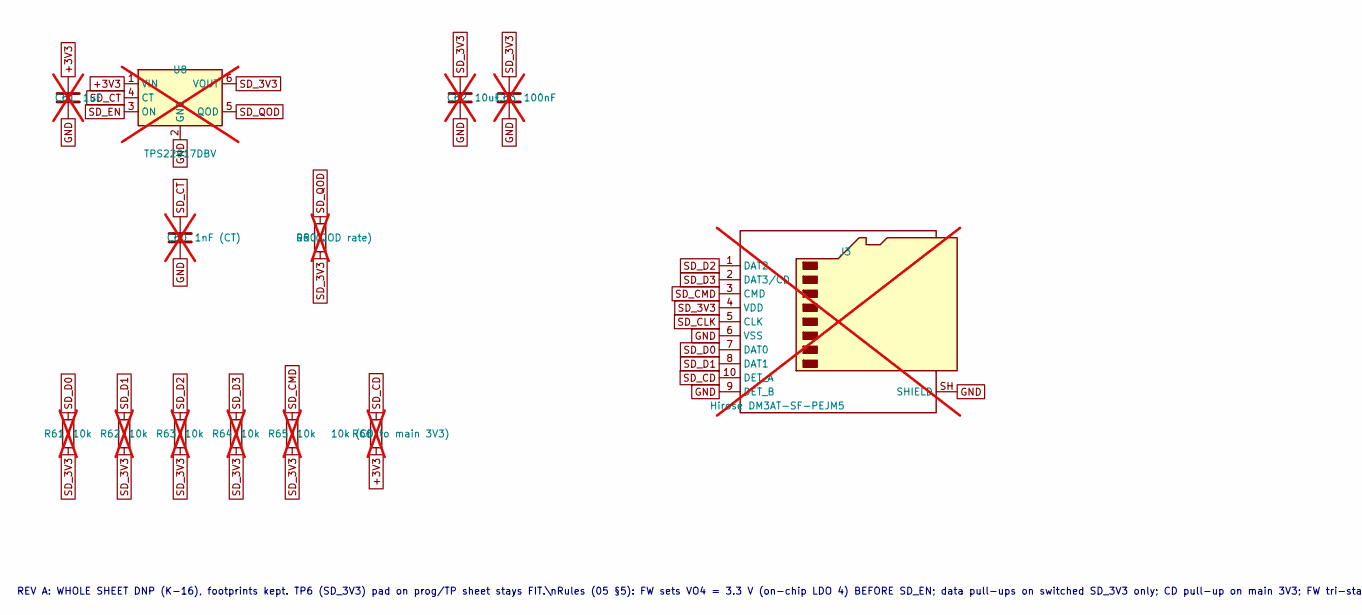
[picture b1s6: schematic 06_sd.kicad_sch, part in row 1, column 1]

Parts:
C60: 1nF (CT); C_0603_1608Metric; not fitted
C61: 1uF; C_0603_1608Metric; not fitted
C62: 10uF; C_0805_2012Metric; not fitted
C63: 100nF; C_0603_1608Metric; not fitted
J3: Hirose DM3AT-SF-PEJM5; microSD_HC_Hirose_DM3AT-SF-PEJM5; not fitted
R60: 0R (QOD rate); R_0603_1608Metric; not fitted
R61, R62, R63, R64, R65: 10k; R_0603_1608Metric; not fitted
R66: 10k (CD to main 3V3); R_0603_1608Metric; not fitted
U8: TPS22917DBV; SOT-23-6; not fitted

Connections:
+3V3: C61.1, R66.2, U8.1 (VIN); also elsewhere on the board
GND: C60.2, C61.2, C62.2, C63.2, J3.6 (VSS), J3.9 (DET_B), J3.SH (SHIELD), U8.2 (GND); also elsewhere on the board
SD_3V3: C62.1, C63.1, J3.4 (VDD), R60.2, R61.2, R62.2, R63.2, R64.2, R65.2, U8.6 (VOUT); also elsewhere on the board
SD_CD: J3.10 (DET_A), R66.1; also elsewhere on the board
SD_CLK: J3.5 (CLK); also elsewhere on the board
SD_CMD: J3.3 (CMD), R65.1; also elsewhere on the board
SD_CT: C60.1, U8.4 (CT)
SD_D0: J3.7 (DAT0), R61.1; also elsewhere on the board
SD_D1: J3.8 (DAT1), R62.1; also elsewhere on the board
SD_D2: J3.1 (DAT2), R63.1; also elsewhere on the board
SD_D3: J3.2 (DAT3/CD), R64.1; also elsewhere on the board
SD_EN: U8.3 (ON); also elsewhere on the board
SD_QOD: R60.1, U8.5 (QOD)

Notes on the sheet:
REV A: WHOLE SHEET DNP (K-16), footprints kept. TP6 (SD_3V3) pad on prog/TP sheet stays FIT.\nRules (05 §5): FW sets VO4 = 3.3 V (on-chip LDO 4) BEFORE SD_EN; data pull-ups on switched SD_3V3 only; CD pull-up on main 3V3; FW tri-states SD pins before SD_EN off.\nsdkconfig: override IDF default SD p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
